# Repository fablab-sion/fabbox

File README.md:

# fabbox
Petit coffre fort à construire avec les moyens d'un Fablab!

<br />Cette œuvre est mise à disposition selon les termes de la <a rel="license" href="http://creativecommons.org/licenses/by-sa/4.0/">Licence Creative Commons Attribution -  Partage dans les Mêmes Conditions 4.0 International</a>.

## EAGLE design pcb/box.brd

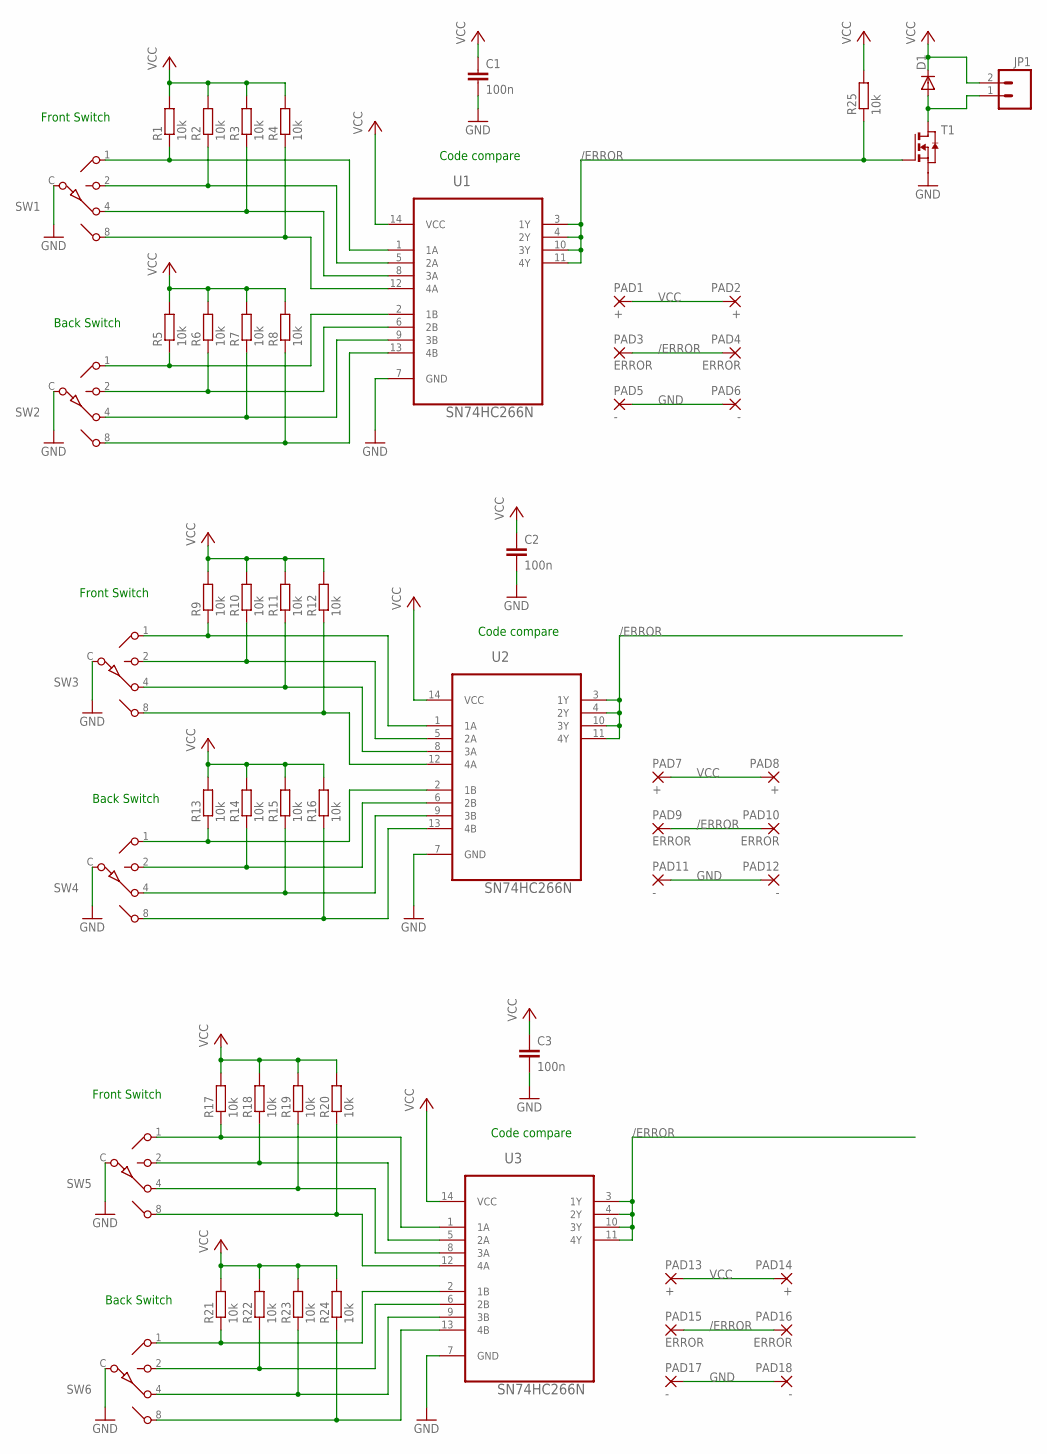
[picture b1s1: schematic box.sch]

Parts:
C1, C2, C3: 100n; C0805
D1: DIODE-DO41-7.6; DO41-7.6
JP1: M02JST-PTH-2; JST-2-PTH
PAD1, PAD2, PAD7, PAD8, PAD13, PAD14: +; 2,15/1,0
PAD3, PAD4, PAD9, PAD10, PAD15, PAD16: ERROR; 2,15/1,0
PAD5, PAD6, PAD11, PAD12, PAD17, PAD18: -; 2,15/1,0
R1, R2, R3, R4, R5, R6, R7, R8, R9, R10, R11, R12, R13, R14, R15, R16, R17, R18, R19, R20, R21, R22, R23, R24, R25: 10k; R0805
SW1, SW2, SW3, SW4, SW5, SW6: ROTARY-SWITCH-10POSMCRM4HAF-10R-V-B; MCRM4HAF
T1: TSM3442; SOT23-6
U1, U2, U3: SN74HC266N; DIP254P762X508-14

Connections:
/ERROR: PAD3.1, PAD4.1, PAD9.1, PAD10.1, PAD15.1, PAD16.1, R25.1, T1.3 (G), U1.3 (1Y), U1.4 (2Y), U1.10 (3Y), U1.11 (4Y), U2.3 (1Y), U2.4 (2Y), U2.10 (3Y), U2.11 (4Y), U3.3 (1Y), U3.4 (2Y), U3.10 (3Y), U3.11 (4Y)
GND: C1.2, C2.2, C3.2, PAD5.1, PAD6.1, PAD11.1, PAD12.1, PAD17.1, PAD18.1, SW1.C, SW2.C, SW3.C, SW4.C, SW5.C, SW6.C, T1.4 (S), U1.7 (GND), U2.7 (GND), U3.7 (GND)
unnamed: R1.1, SW1.1, U1.1 (1A)
unnamed: R2.1, SW1.2, U1.5 (2A)
unnamed: R3.1, SW1.4, U1.8 (3A)
unnamed: R4.1, SW1.8, U1.12 (4A)
unnamed: D1.A, JP1.1, T1.1 (D), T1.2 (D), T1.5 (D), T1.6 (D)
unnamed: R5.1, SW2.1, U1.2 (1B)
unnamed: R6.1, SW2.2, U1.6 (2B)
unnamed: R7.1, SW2.4, U1.9 (3B)
unnamed: R8.1, SW2.8, U1.13 (4B)
unnamed: R9.1, SW3.1, U2.1 (1A)
unnamed: R10.1, SW3.2, U2.5 (2A)
unnamed: R11.1, SW3.4, U2.8 (3A)
unnamed: R12.1, SW3.8, U2.12 (4A)
unnamed: R13.1, SW4.1, U2.2 (1B)
unnamed: R14.1, SW4.2, U2.6 (2B)
unnamed: R15.1, SW4.4, U2.9 (3B)
unnamed: R16.1, SW4.8, U2.13 (4B)
unnamed: R17.1, SW5.1, U3.1 (1A)
unnamed: R18.1, SW5.2, U3.5 (2A)
unnamed: R19.1, SW5.4, U3.8 (3A)
unnamed: R20.1, SW5.8, U3.12 (4A)
unnamed: R21.1, SW6.1, U3.2 (1B)
unnamed: R22.1, SW6.2, U3.6 (2B)
unnamed: R23.1, SW6.4, U3.9 (3B)
unnamed: R24.1, SW6.8, U3.13 (4B)
VCC: C1.1, C2.1, C3.1, D1.C, JP1.2, PAD1.1, PAD2.1, PAD7.1, PAD8.1, PAD13.1, PAD14.1, R1.2, R2.2, R3.2, R4.2, R5.2, R6.2, R7.2, R8.2, R9.2, R10.2, R11.2, R12.2, R13.2, R14.2, R15.2, R16.2, R17.2, R18.2, R19.2, R20.2, R21.2, R22.2, R23.2, R24.2, R25.2, U1.14 (VCC), U2.14 (VCC), U3.14 (VCC)

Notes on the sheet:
Front Switch
Back Switch
Code compare

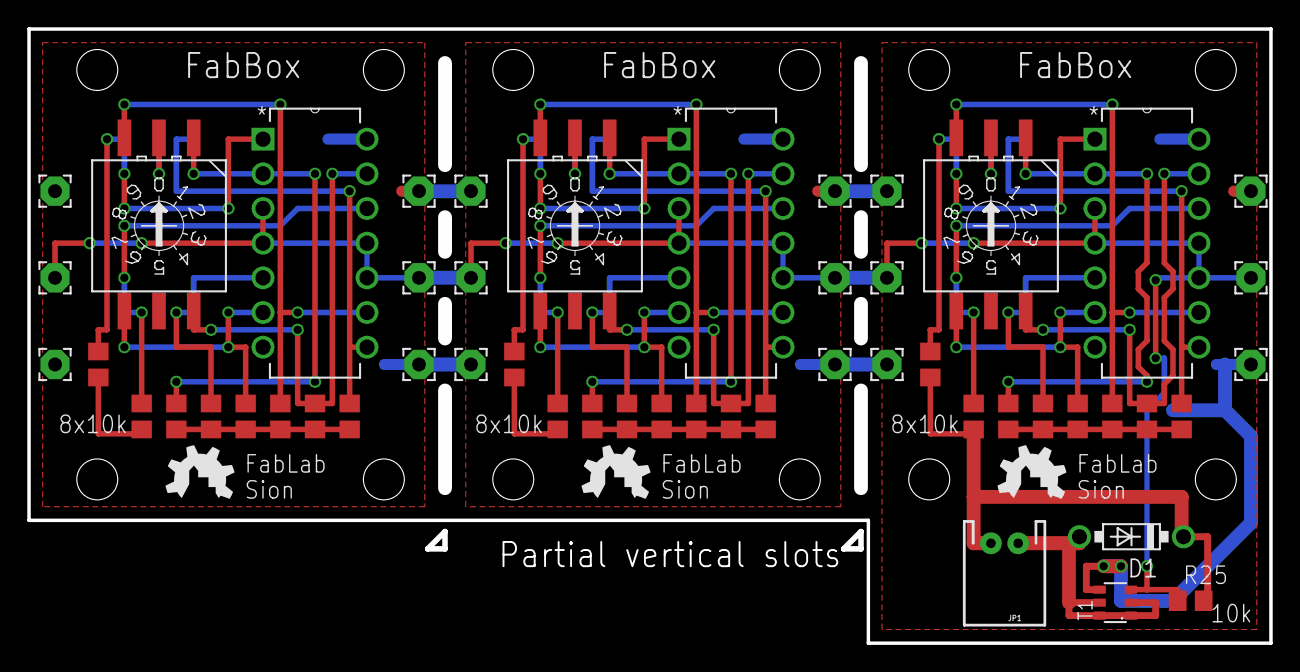
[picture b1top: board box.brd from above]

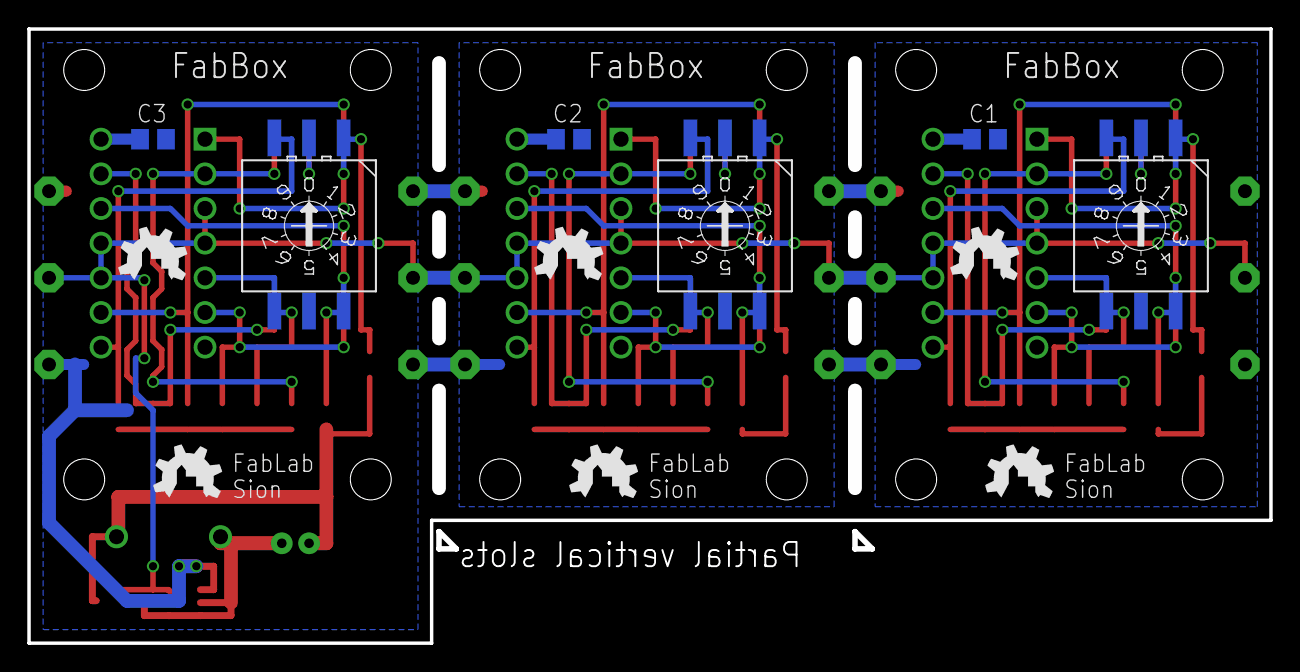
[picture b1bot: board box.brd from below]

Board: 2 copper layers, 91.0 x 45.0 mm, 67 parts (12 on the bottom side), 28 nets.

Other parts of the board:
E$1, E$3, E$5: LOGO_200
E$2, E$4, E$6: LOGO_200_TEXT
U$1, U$2, U$3: LOGO_200_TEXT

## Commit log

2016-07-22 Add license.
2016-08-17 Add pcb sources.
2016-08-17 Add mechanicals.
2016-10-25 Add coil holder.
2018-05-09 Fix wrong dxfs.

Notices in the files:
parts and their libraries:
SparkFun-Connectors: Licensing: Creative Commons ShareAlike 4.0 International - https://creativecommons.org/licenses/by-sa/4.0
